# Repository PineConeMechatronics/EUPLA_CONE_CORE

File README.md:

# EUPLA_CONE_CORE
Academic hardware development for the EUPLA_CONE_CORE project, including manufacturing files and sensor testing scripts.

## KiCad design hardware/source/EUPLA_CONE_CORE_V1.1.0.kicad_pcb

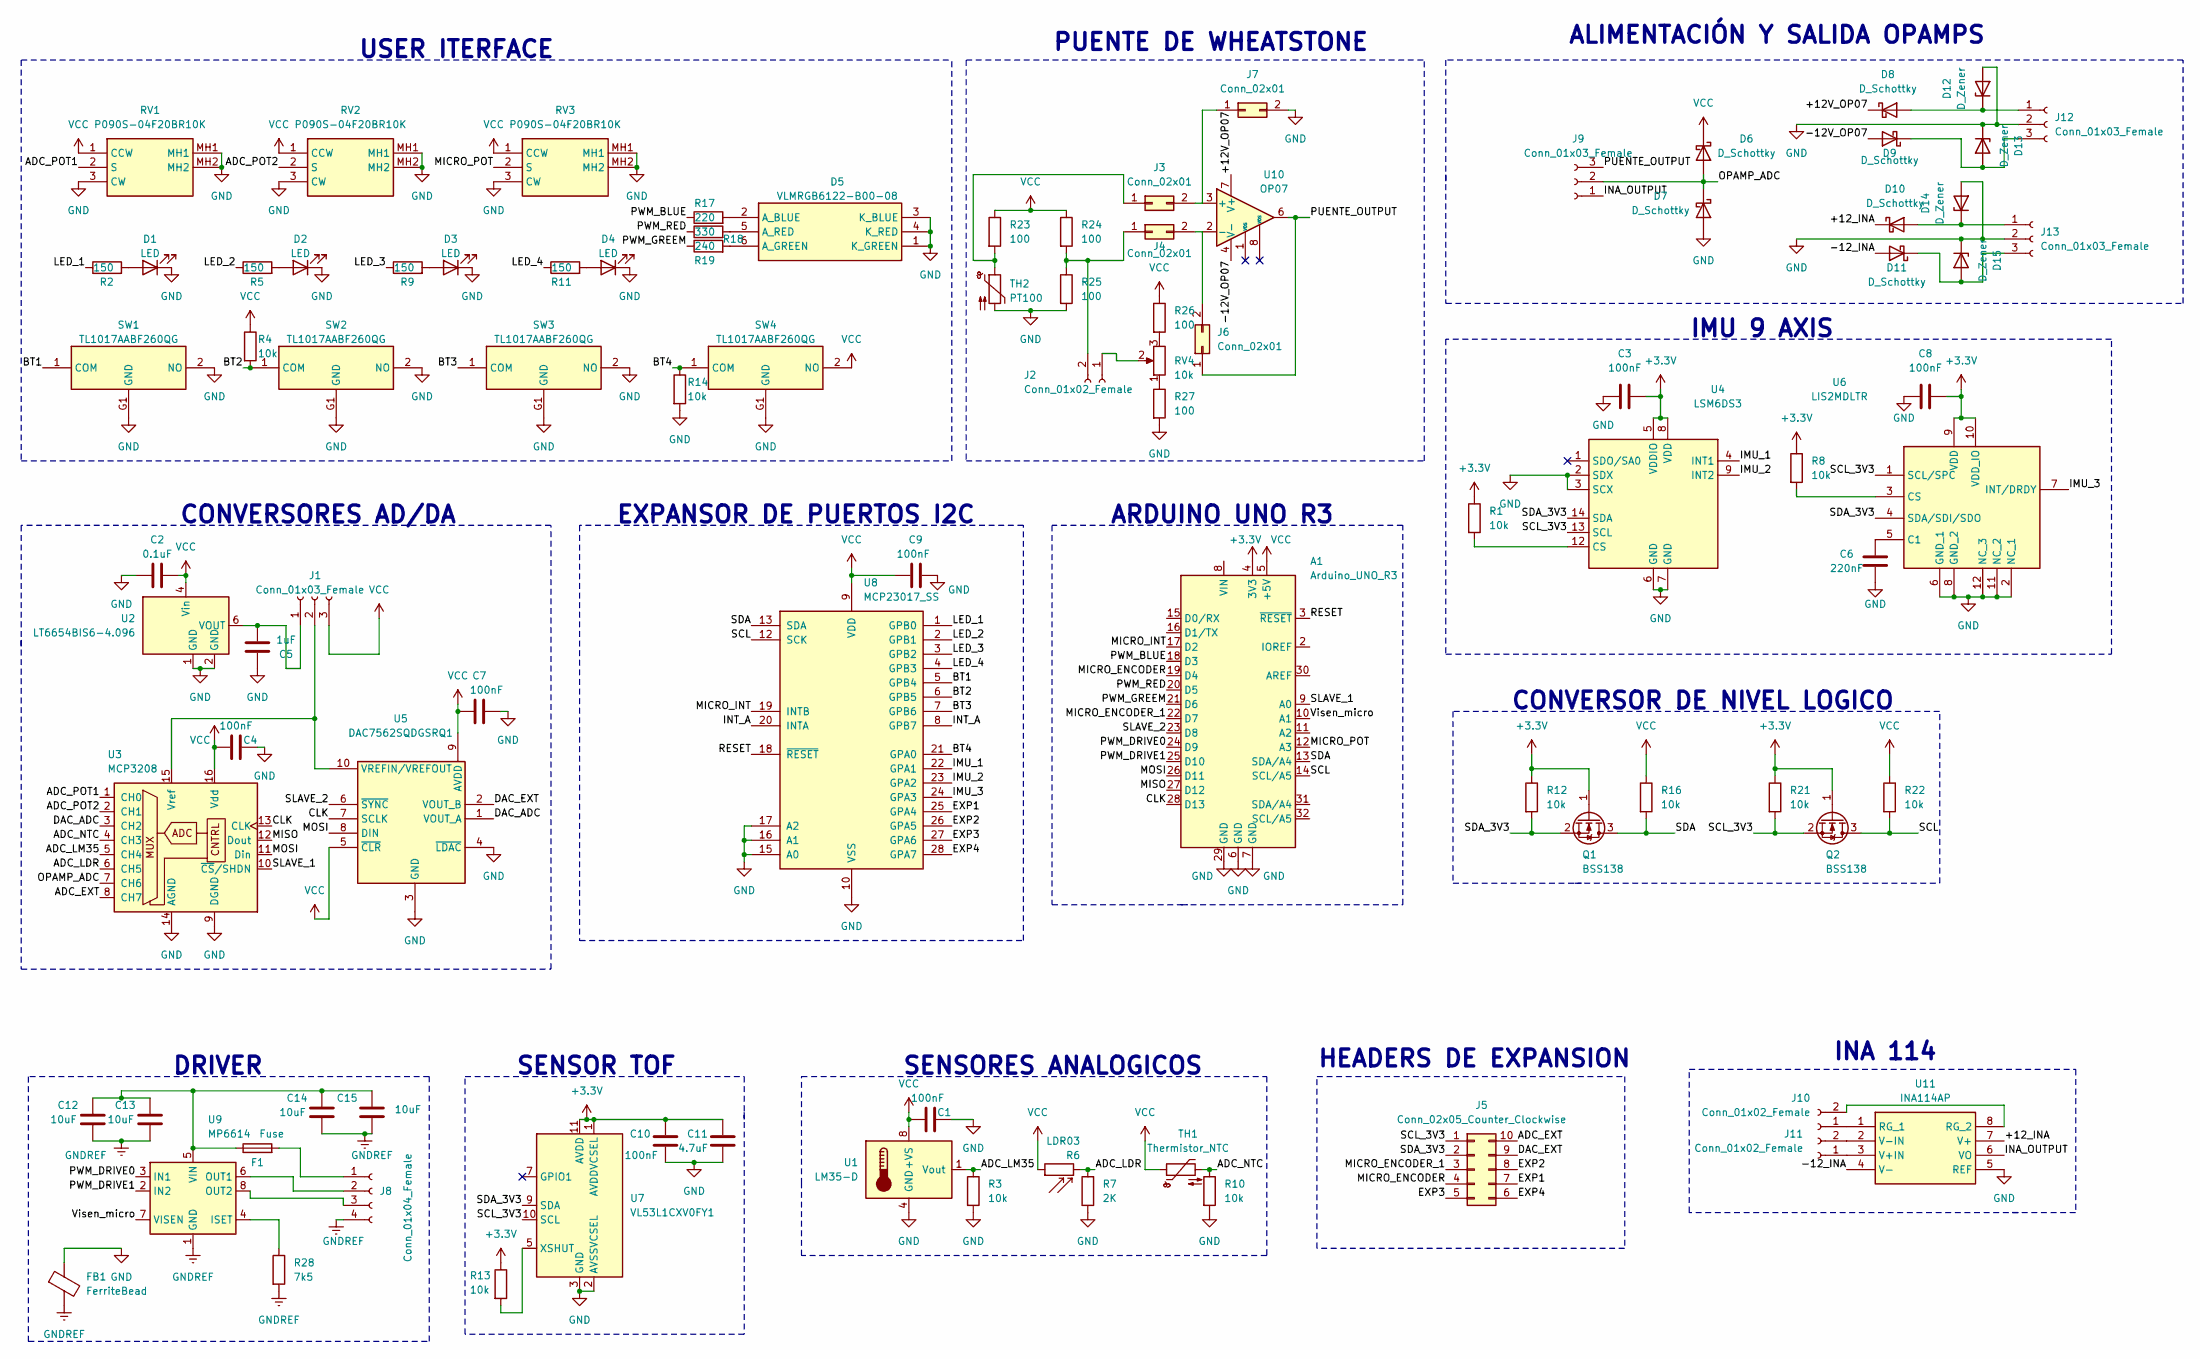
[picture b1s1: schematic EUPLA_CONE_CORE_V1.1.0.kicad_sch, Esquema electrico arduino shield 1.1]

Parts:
A1: Arduino_UNO_R3
C1, C3, C4, C7, C8, C9, C10: 100nF; C_0603_1608Metric
C2: 0.1uF; C_0603_1608Metric
C5: 1uF; C_0603_1608Metric
C6: 220nF; C_0603_1608Metric
C11: 4.7uF; C_0603_1608Metric
C12, C13, C14, C15: 10uF; C_0603_1608Metric
D1, D2, D3, D4: LED; LED_0603_1608Metric
D5: VLMRGB6122-B00-08; VLMRGB6122B0008; Manufacturer_Part_Number VLMRGB6122-B00-08
D6, D7, D8, D9, D10, D11: D_Schottky; CUS10S40H3F
D12, D13, D14, D15: D_Zener; D_SOD-123
F1: Fuse; Fuse_0603_1608Metric
FB1: FerriteBead; SMDC030F2
J1, J9, J12, J13: Conn_01x03_Female; PinHeader_1x03_P2.54mm_Vertical
J2: Conn_01x02_Female; PinHeader_1x02_P2.54mm_Vertical
J3, J4, J6, J7: Conn_02x01; PinHeader_1x02_P2.54mm_Vertical
J5: Conn_02x05_Counter_Clockwise; PinSocket_2x05_P2.54mm_Vertical
J8: Conn_01x04_Female; PRT15519
J10, J11: Conn_01x02_Female; PinSocket_1x02_P2.54mm_Vertical
Q1, Q2: BSS138; SOT-23
R1, R3, R4, R8, R10, R12, R13, R14, R16, R21, R22: 10k; R_0603_1608Metric
R2, R5, R9, R11: 150; R_0603_1608Metric
R6: LDR03; R_LDR_10x8.5mm_P7.6mm_Vertical
R7: 2K; R_0603_1608Metric
R17: 220; R_0603_1608Metric
R18: 330; R_0603_1608Metric
R19: 240; R_0603_1608Metric
R23, R24, R25, R26, R27: 100; R_0603_1608Metric
R28: 7k5; R_0603_1608Metric
RV1, RV2, RV3: P090S-04F20BR10K; P090S04F20BR10K; Mouser Part Number 858-P090S04F20BR10K
RV4: 10k; 3296Y11103LF
SW1, SW2, SW3, SW4: TL1017AABF260QG; Mouser Part Number 612-TL1017AABF260QG
TH1: Thermistor_NTC; R_0603_1608Metric
TH2: PT100; RESC2214X70N
U1: LM35-D; SOIC-8_3.9x4.9mm_P1.27mm
U2: LT6654BIS6-4.096; S_6_ADI
U3: MCP3208; SOIC127P600X175-16N
U4: LSM6DS3; LGA-14_3x2.5mm_P0.5mm_LayoutBorder3x4y
U5: DAC7562SQDGSRQ1; SOP50P490X110-10N; Mouser Part Number 595-DAC7562SQDGSRQ1
U6: LIS2MDLTR; LGA-12; Mouser Part Number 511-LIS2MDLTR
U7: VL53L1CXV0FY1; ST_VL53L1x
U8: MCP23017_SS; SOP65P780X200-28N
U9: MP6614; SOIC-8-1EP_3.9x4.9mm_P1.27mm_EP2.62x3.51mm
U10: OP07; SOIC127P780X200-8N
U11: INA114AP; DIP794W53P254L959H508Q8N; Mouser Part Number 595-INA114AP

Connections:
+3.3V: A1.4 (3V3), C3.2, C8.2, C10.2, C11.2, Q1.1 (G), Q2.1 (G), R1.1, R8.1, R12.1, R13.1, R21.1, U4.5 (VDDIO), U4.8 (VDD), U6.9 (VDD), U6.10 (VDD_IO), U7.1 (AVDDVCSEL), U7.11 (AVDD)
/+12V_OP07: D8.1 (K), U10.7 (V+)
/+12_INA: D10.1 (K), U11.7 (V+)
/-12V_OP07: D9.2 (A), U10.4 (V-)
/-12_INA: D11.2 (A), U11.4 (V-)
/ADC_EXT: J5.10, U3.8 (CH7)
/ADC_LDR: R6.2, R7.2, U3.6 (CH5)
/ADC_LM35: R3.1, U1.1 (Vout), U3.5 (CH4)
/ADC_NTC: R10.1, TH1.2, U3.4 (CH3)
/ADC_POT1: RV1.2 (S), U3.1 (CH0)
/ADC_POT2: RV2.2 (S), U3.2 (CH1)
/BT1: SW1.1 (COM), U8.5 (GPB4)
/BT2: R4.2, SW2.1 (COM), U8.6 (GPB5)
/BT3: SW3.1 (COM), U8.7 (GPB6)
/BT4: R14.1, SW4.1 (COM), U8.21 (GPA0)
/CLK: A1.28 (D13), U3.13 (CLK), U5.7 (SCLK)
/DAC_ADC: U3.3 (CH2), U5.1 (VOUT_A)
/DAC_EXT: J5.9, U5.2 (VOUT_B)
/EXP1: J5.7, U8.25 (GPA4)
/EXP2: J5.8, U8.26 (GPA5)
/EXP3: J5.5, U8.27 (GPA6)
/EXP4: J5.6, U8.28 (GPA7)
/IMU_1: U4.4 (INT1), U8.22 (GPA1)
/IMU_2: U4.9 (INT2), U8.23 (GPA2)
/IMU_3: U6.7 (INT/DRDY), U8.24 (GPA3)
/INA_OUTPUT: J9.1, U11.6 (VO)
/INT_A: U8.8 (GPB7), U8.20 (INTA)
/LED_1: R2.1, U8.1 (GPB0)
/LED_2: R5.1, U8.2 (GPB1)
/LED_3: R9.1, U8.3 (GPB2)
/LED_4: R11.1, U8.4 (GPB3)
/MICRO_ENCODER: A1.19 (D4), J5.4
/MICRO_ENCODER_1: A1.22 (D7), J5.3
/MICRO_INT: A1.17 (D2), U8.19 (INTB)
/MICRO_POT: A1.12 (A3), RV3.2 (S)
/MISO: A1.27 (D12), U3.12 (Dout)
/MOSI: A1.26 (D11), U3.11 (Din), U5.8 (DIN)
/OPAMP_ADC: D6.2 (A), D7.1 (K), J9.2, U3.7 (CH6)
/PUENTE_OUTPUT: J6.1, J9.3, U10.6
/PWM_BLUE: A1.18 (D3), R17.1
/PWM_DRIVE0: A1.24 (D9), U9.3 (IN1)
/PWM_DRIVE1: A1.25 (D10), U9.2 (IN2)
/PWM_GREEM: A1.21 (D6), R19.1
/PWM_RED: A1.20 (D5), R18.1
/RESET: A1.3 (~RESET), U8.18 (~RESET)
/SCL: A1.14 (SCL/A5), Q2.3 (D), R22.2, U8.12 (SCK)
/SCL_3V3: J5.1, Q2.2 (S), R21.2, U4.13 (SCL), U6.1 (SCL/SPC), U7.10 (SCL)
/SDA: A1.13 (SDA/A4), Q1.3 (D), R16.2, U8.13 (SDA)
/SDA_3V3: J5.2, Q1.2 (S), R12.2, U4.14 (SDA), U6.4 (SDA/SDI/SDO), U7.9 (SDA)
/SLAVE_1: A1.9 (A0), U3.10 (~CS/SHDN)
/SLAVE_2: A1.23 (D8), U5.6 (~SYNC)
/Visen_micro: A1.10 (A1), U9.7 (VISEN)
GND: A1.6 (GND), A1.7 (GND), A1.29 (GND), C1.2, C2.1, C3.1, C4.2, C5.1, C6.2, C7.2, C8.1, C9.2, C10.1, C11.1, D1.1 (K), D2.1 (K), D3.1 (K), D4.1 (K), D5.1 (K_GREEN), D5.3 (K_BLUE), D5.4 (K_RED), D7.2 (A), D12.2 (A), D13.1 (K), D14.2 (A), D15.1 (K), FB1.1, J7.2, J12.2, J13.2, R3.2, R7.1, R10.2, R14.2, R25.2, R27.2, RV1.3 (CW), RV1.MH1, RV1.MH2, RV2.3 (CW), RV2.MH1, RV2.MH2, RV3.3 (CW), RV3.MH1, RV3.MH2, SW1.2 (NO), SW1.G1 (GND), SW2.2 (NO), SW2.G1 (GND), SW3.2 (NO), SW3.G1 (GND), SW4.G1 (GND), TH2.2, U1.4 (GND), U2.1 (GND), U2.2 (GND), U3.9 (DGND), U3.14 (AGND), U4.2 (SDX), U4.3 (SCX), U4.6 (GND), U4.7 (GND), U5.3 (GND), U5.4 (~LDAC), U6.2 (NC_1), U6.6 (GND_1), U6.8 (GND_2), U6.11 (NC_2), U6.12 (NC_3), U7.2 (AVSSVCSEL), U7.3 (GND), U7.4 (GND), U7.6 (GND), U7.12 (GND), U8.10 (VSS), U8.15 (A0), U8.16 (A1), U8.17 (A2), U11.5 (REF); also elsewhere on the board
GNDREF: C12.2, C13.2, C14.2, C15.2, FB1.2, J8.4, R28.2, U9.1 (GND), U9.9 (GND)
unnamed: D1.2 (A), R2.2
unnamed: D2.2 (A), R5.2
unnamed: D3.2 (A), R9.2
unnamed: D4.2 (A), R11.2
unnamed: D5.2 (A_BLUE), R17.2
unnamed: D5.6 (A_GREEN), R19.2
unnamed: D5.5 (A_RED), R18.2
unnamed: D10.2 (A), D14.1 (K), J13.1
unnamed: D11.1 (K), D15.2 (A), J13.3
unnamed: D8.2 (A), D12.1 (K), J12.1
unnamed: D9.1 (K), D13.2 (A), J12.3
unnamed: C5.2, J1.1, U2.6 (VOUT)
unnamed: J1.2, U3.15 (Vref), U5.10 (VREFIN/VREFOUT)
unnamed: J2.1, RV4.2
unnamed: J2.2, J4.1, R24.2, R25.1
unnamed: J3.1, R23.2, TH2.1
unnamed: J3.2, J7.1, U10.3 (+)
unnamed: J4.2, J6.2, U10.2 (-)
unnamed: F1.2, J8.1
unnamed: J8.2, U9.6 (OUT1)
unnamed: J8.3, U9.8 (OUT2)
unnamed: J10.1, U11.1 (RG_1)
unnamed: J10.2, U11.8 (RG_2)
unnamed: J11.1, U11.3 (V+IN)
unnamed: J11.2, U11.2 (V-IN)
unnamed: R26.2, RV4.3
unnamed: R27.1, RV4.1
unnamed: R1.2, U4.12 (CS)
unnamed: C6.1, U6.5 (C1)
unnamed: R8.2, U6.3 (CS)
unnamed: R13.2, U7.5 (XSHUT)
unnamed: R28.1, U9.4 (ISET)
unnamed: C12.1, C13.1, C14.1, C15.1, F1.1, U9.5 (VIN)
VCC: A1.5 (+5V), C1.1, C2.2, C4.1, C7.1, C9.1, D6.1 (K), J1.3, R4.1, R6.1, R16.1, R22.1, R23.1, R24.1, R26.1, RV1.1 (CCW), RV2.1 (CCW), RV3.1 (CCW), SW4.2 (NO), TH1.1, U1.8 (+VS), U2.4 (Vin), U3.16 (Vdd), U5.5 (~CLR), U5.9 (AVDD), U8.9 (VDD)

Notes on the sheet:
IMU 9 AXIS
CONVERSORES AD/DA
ALIMENTACIÓN Y SALIDA OPAMPS
EXPANSOR DE PUERTOS I2C
USER ITERFACE
DRIVER
PUENTE DE WHEATSTONE
SENSOR TOF
HEADERS DE EXPANSION
INA 114
ARDUINO UNO R3
CONVERSOR DE NIVEL LOGICO
SENSORES ANALOGICOS

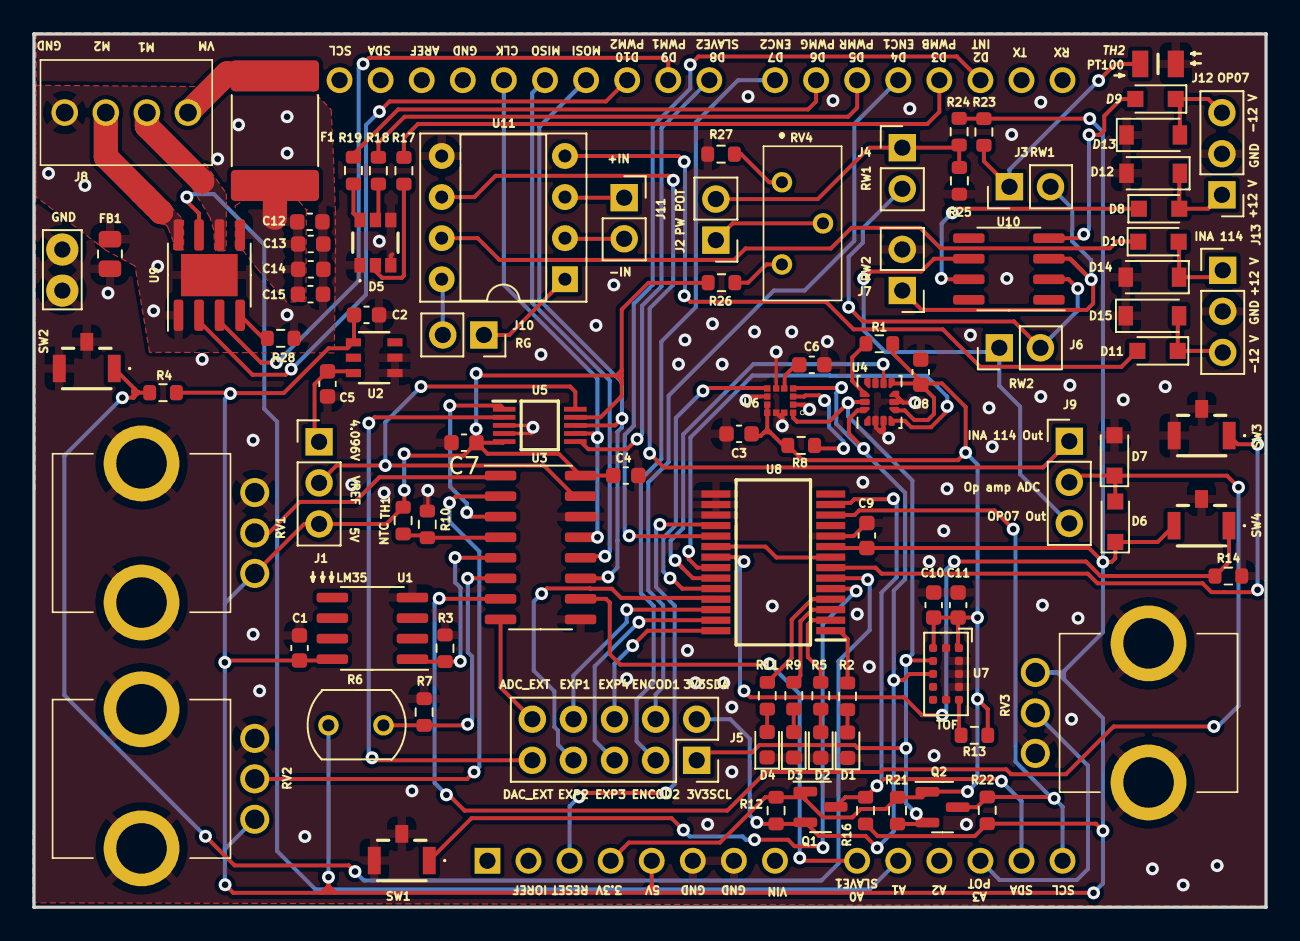
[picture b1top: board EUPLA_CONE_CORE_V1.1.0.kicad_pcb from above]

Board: 2 copper layers, 76.2 x 54.0 mm, 96 parts (1 on the bottom side), 88 nets.

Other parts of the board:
GND: TestPoint_Bridge_Pitch2.54mm_Drill1.0mm

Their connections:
GND: GND.1; also elsewhere on the board

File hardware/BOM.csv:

Designator;quantity;value/description;Footprint;Part Number;supplier;;;;
R1,R3,R4,R8,R10,R12,R13,R16,R21,R22,R14;11;10k Ohms resistor;0603;ESR03EZPD1002 ;Mouser electronics;;;;
R2,R5,R9,R11;4;160 Ohms resistor ;0603;ESR03EZPF1600 ;Mouser electronics;;;;
R17;1;220 Ohms resistor;0603;ESR03EZPF2200;Mouser electronics;;;;
R18;1;330 Ohms resistor;0603;ESR03EZPF3300;Mouser electronics;;;;
R19;1;240 Ohms resistor;0603;ESR03EZPF2400;Mouser electronics;;;;
R28;1;7,5k  Ohms resistor;0603;ESR03EZPD7501 ;Mouser electronics;;;;
R7;1;2k Ohms resistor;0603;ESR03EZPD2001;Mouser electronics;;;;
R23-R25;3;100 Ohms 0,01% resistor ;0603;APC0603T100RZ ;Mouser electronics;;;;
R26, R27;2;100 Ohms resistor;0603;ESR03EZPF1000 ;Mouser electronics;;;;
R6;1;LDR Ligth Dependent Resistor;5.1 mm x 4.3 mm x 2 mm;PDV-P8103 ;Mouser electronics;;;;
C1-C4, C7-C10;8;100nF ceramic capacitor;0603; C0603F104K3RACTU  ;Mouser electronics;;;;
C5;1;1 uF ;0603; MSASG168SB5105KTNA01 ;Mouser electronics;;;;
C6;1;220 nF ceramic capacitor;0603;MSAYU168BLD224KTNA01 ;Mouser electronics;;;;
C11;1;4,7 uF ceramic capacitor;0603;MSASL168BD7475KTCA01 ;Mouser electronics;;;;
C12-C15;4;10 uF ceramic capacitor;0603;ZRB18AR61E106KE01L ;Mouser electronics;;;;
D1-D4;4;RED LED Diode;0603;SML-D12U8WT86 ;Mouser electronics;;;;
D5;1;RGB Diode;Custom footprint;VLMRGB6122-B00-08;Mouser electronics;;;;
D6-D11;6;Schottky Diode;SOD-323;CUS10S40,H3F ;Mouser electronics;;;;
D12-D15;4;Zenner Diode;SOD-123;MMSZ5245C-HE3_A-08 ;Mouser electronics;;;;
SW1-SW4;4;SMD Switches;Custom footprint;TL1017AABF260QG ;Mouser electronics;;;;
RV1-RV3;3;10K potenciometer ;Custom footprint;P090S-04F20BR10K;Mouser electronics;;;;
RV4;1;10k Trimmer;Custom footprint;3296Y-11-103LF ;Mouser electronics;;;;
Q1,Q2;2;N-Channel MOSFET;SOT-23;BSS138;Mouser electronics;;;;
J1,J9;2;PinHeader  01x03;1x03_P2,54mm_Vertical;1-826629-2;Mouser electronics;;;;
J2;1;PinHeader 01x02;1x02_P2,54mm_Vertical;1-826629-2;Mouser electronics;;;;
J5;1;PinSockect 02x05;2x05_P2,54mm_Vertical;HIF3H-10DA-2.54DSA(61);DigiKey;;;;
J3,J4,J6,J7,J10,J11;6;PinSockect 01x02;1x02_P2,54mm_Vertical;PPPC021LFBN-RC;DigiKey;;;;
J2,J13;2;PinSockect 01x03;1x03_P2,54mm_Vertical;PPTC031LFBN-RC;DigiKey;;;;
J8;1;header driver ;Custom footprint;1546215-4 ;Mouser electronics;;;;
TH1;1;Thermistor NTC;0603;NTCGS103JX103DT7 ;Mouser electronics;;;;
TH2;1;RTD PT100 ;Custom footprint;32207605;Mouser electronics;;;;
U1;1;LM35 Temperature sensor;SOIC-8;LM35DMX/NOPB ;Mouser electronics;;;;
U2;1;Voltaje reference 4,096;SOT-23-6;LT6654BIS6-4.096#TRMPBF;Mouser electronics;;;;
U3;1;ADC Converter 8 channels;SOIC-16;MCP3208-BI/SL;Mouser electronics;;;;
U4;1;IMU 6 axis (acelerometre + Gyro);LGA-14L;LSM6DSO32XTR;Mouser electronics;;;;
U5;1;DAC converter 2 chanels;MSOP-10;DAC7562SQDGSRQ1;Mouser electronics;;;;
U6;1;Magnetrometer 3 axis;LGA-12;LIS2MDLTR;Mouser electronics;;;;
U7;1; Time  of  Fligth sensor ;Custom footprint;VL53L1CXV0FY/1;Mouser electronics;;;;
U8;1;I/O Expanders I₂C;SSOP-28;MCP23017T-E/SS;Mouser electronics;;;;
U9;1;Driver H bridge;SOIC-8EP;MP6614GN-P;Mouser electronics;;;;
U10;1;OP AMP OP07;SOIC-8;OP07CSZ;Mouser electronics;;;;
U11;1;Socket INA114;DIP-8;1-2199298-2;Mouser electronics;;;;
U11' ;1;INA 114;PDIP-8;INA114AP;Mouser electronics;;;;
A1 ;1;Shield stacking headers for Arduino;Arduino R3;;Adafruit;;;;
